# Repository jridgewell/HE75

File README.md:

# HE75

A standard 60% kebyoard (GH60 compatible) with 75 hall effects keys and an ortholinear layout.

## Prior Art

While this keyboard is my own design, I pulled from many prior keyboard designs to figure out 60% layouts and how to layout hall effect sensors.

- [MoonBoard](https://github.com/certainly1182/MoonBoard), which I used heavily for routing patterns, schematic design, and even to find code to program QMK.
- [Void Switch 65%](https://github.com/riskable/void_switch_65_pct) (and the 2 begining videos [part 1](https://www.youtube.com/watch?v=TfKz_FbZWLQ) and [part 2](https://www.youtube.com/watch?v=sFR6E_Ejot0)), for giving me a starting point.
- [HE8](https://github.com/peppapighs/HE8) (and his [writeup](https://old.reddit.com/r/MechanicalKeyboards/comments/1glk0dc/i_made_a_hall_effect_macropad_long_writeup_below/)) to confirm components work.

I also used a few community assets to start the design:
- https://github.com/ebastler/marbastlib for switches and stabalizers footprints.
- https://github.com/ai03-2725/JP60 for an up-to-date GH60 shell layout.

# Constraints while designing

1. Must fit into a 60% keyboard case
2. Must use an ortholinear layout
3. Must use hall effect keys

I bought a [Wooting 60HE module](https://wooting.io/wooting-60he-module) and case, but I just can't stand the standard keyboard layout after using a split-ortho board for years. This is my attempt to cram an ortholinear layout into the same case, keeping it as close to a normal row staggered layout as possible. I do need occasional 1-handed access to right-hand side of the keyboard, I'm not after a mock split.

The first major issue is mouting positions for GH60 keyboards (marked in red):

When putting an ortholinear layout over top of that, several of the keys conflict:

If I were using standard MX key switches, this would only require rotating those keys 90% and skipping the screws in those locations. But with a hall effect keyboard, there's a hall effect sensor on the backside of the PCB occupying the same space as the screw mount. I need to move it so that it doesn't short out or get damaged when inserting the keyboard into the case. So for three keys (Q, H, and \), the sensor is roughly 1mm out of alignment with the key switch's magnet. Hopefully this'll be ok.

# Next Steps

I haven't ordered the first set of boards yet. JLCPCB estimates $47 for the first 5 PCBs, and $142 to get them assembled. I'm hoping someone will review the design before I send it off, I'm very new to this.

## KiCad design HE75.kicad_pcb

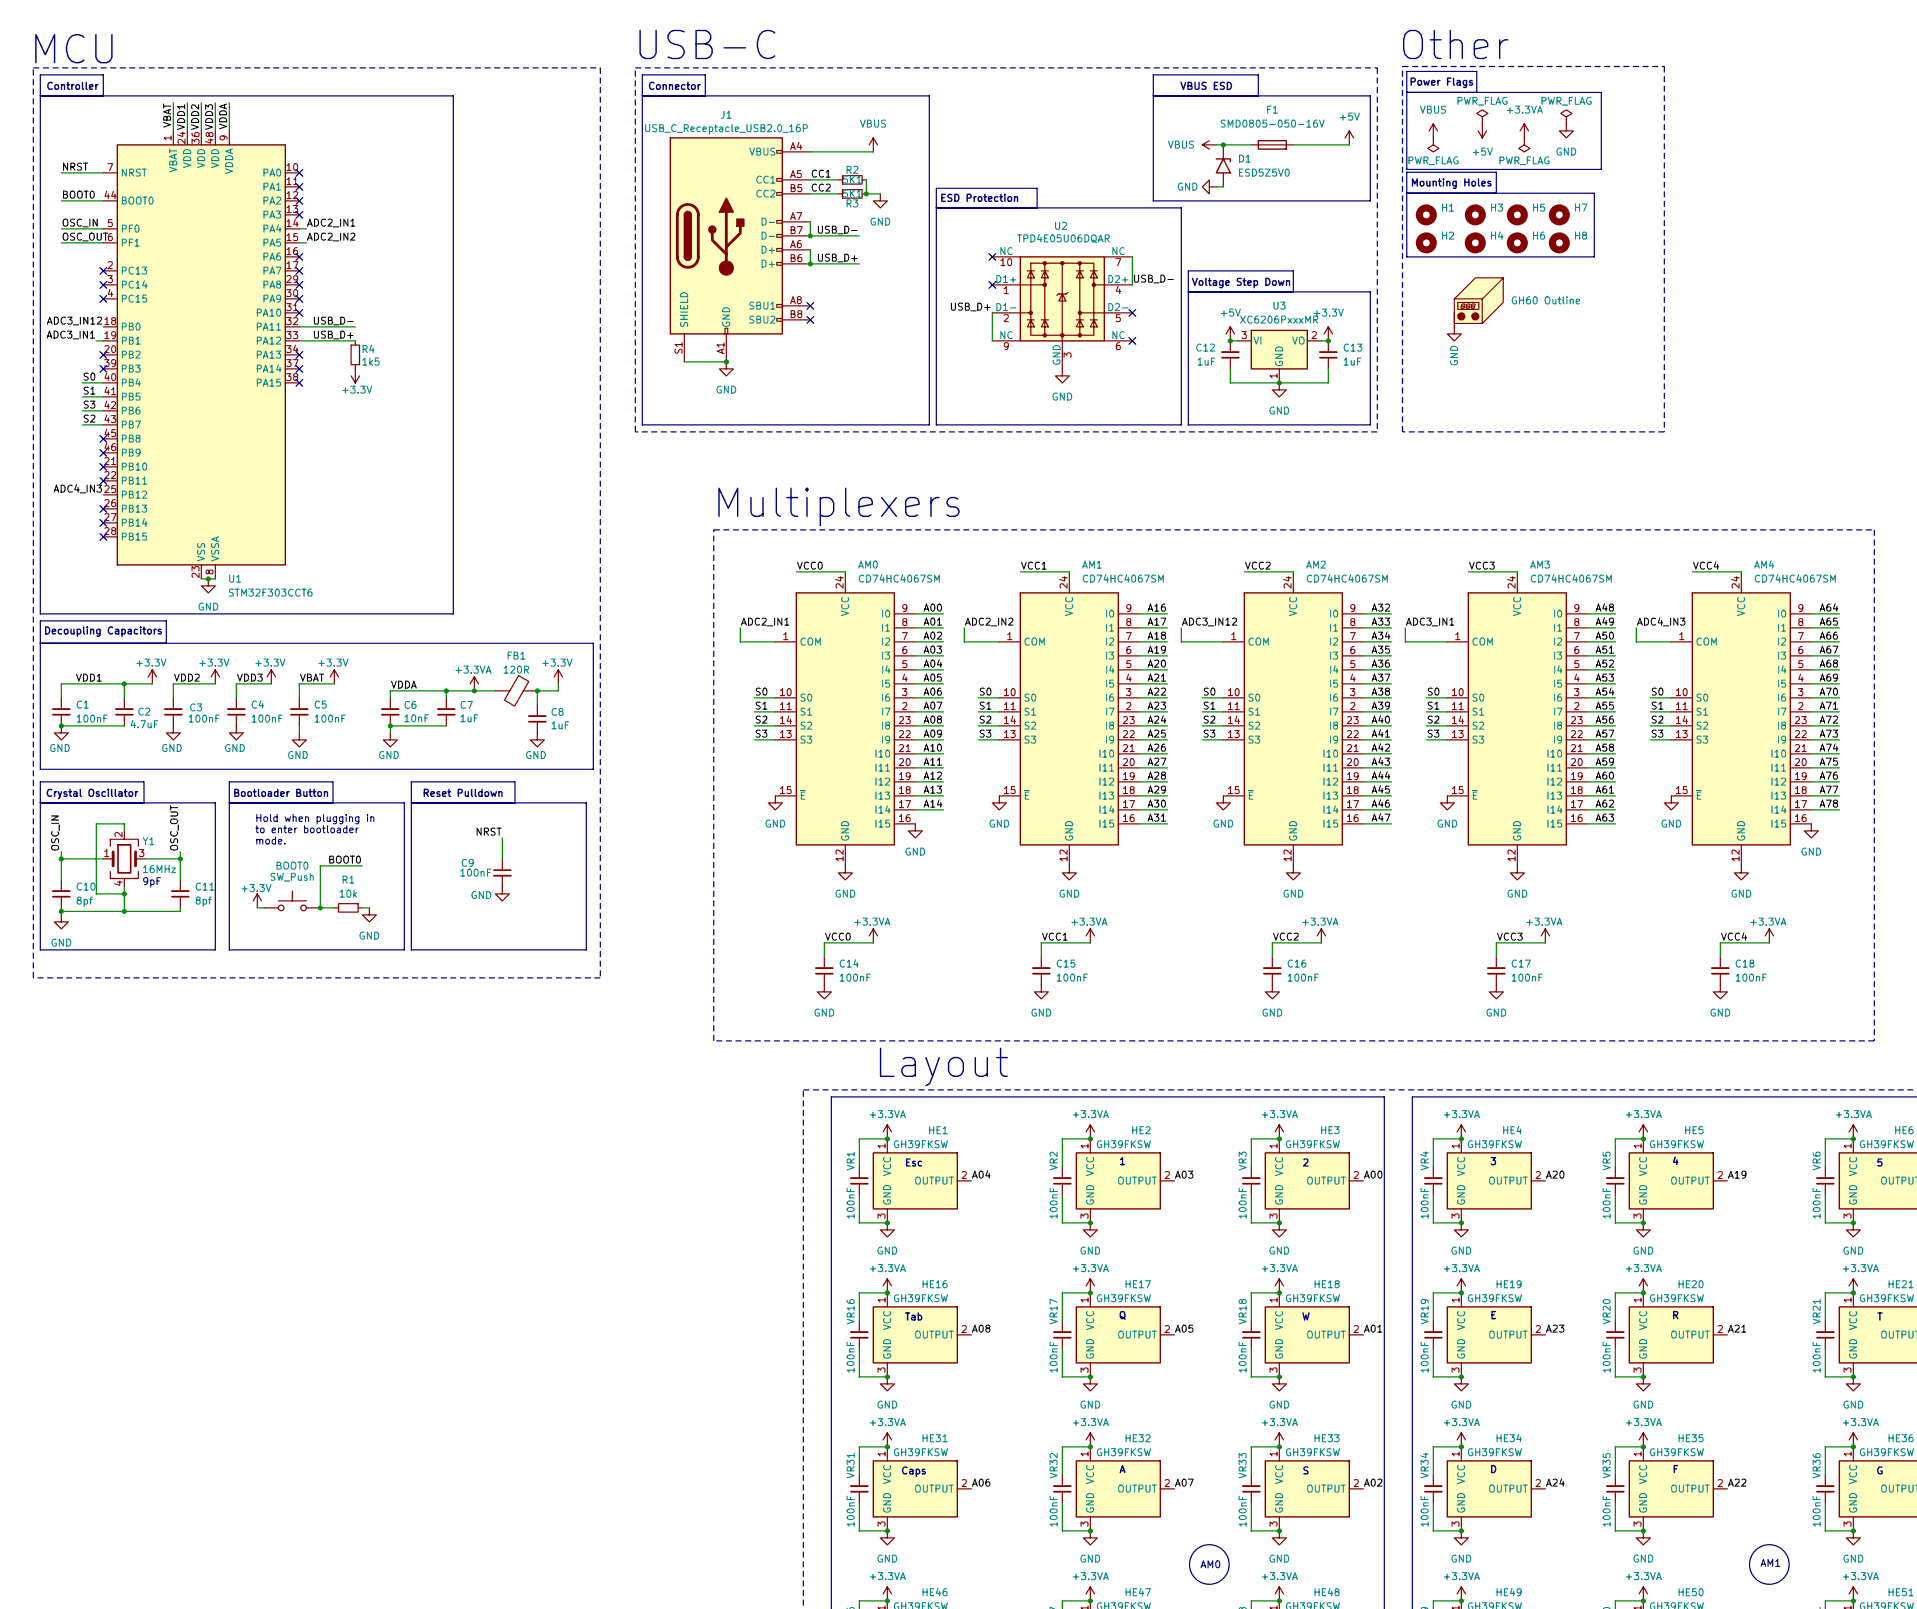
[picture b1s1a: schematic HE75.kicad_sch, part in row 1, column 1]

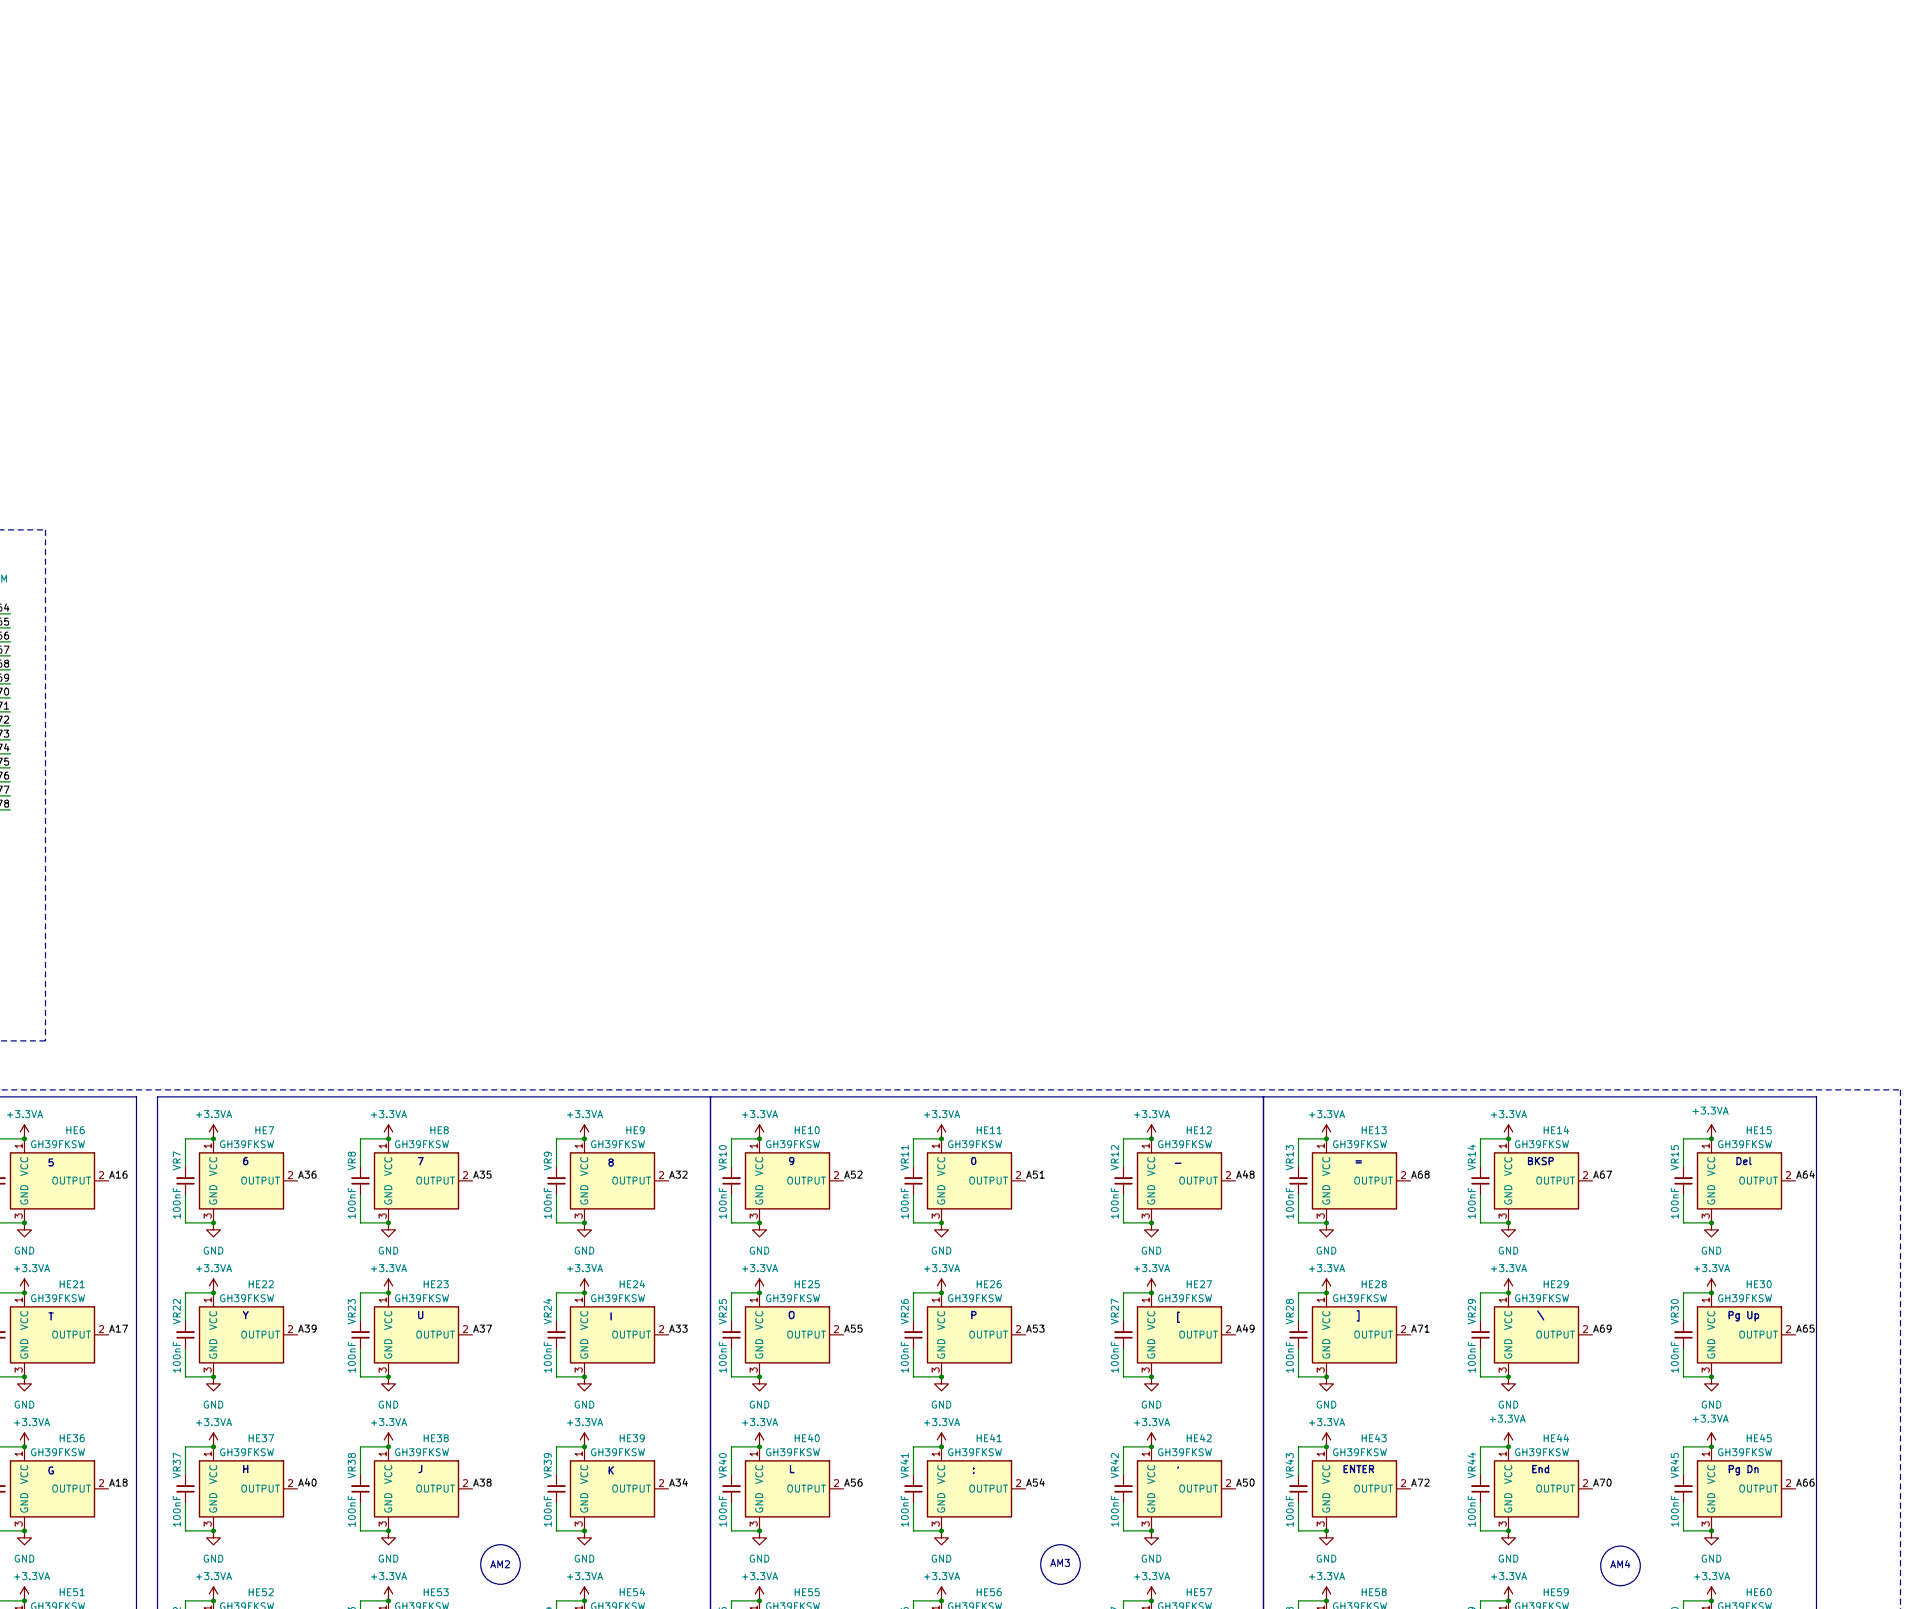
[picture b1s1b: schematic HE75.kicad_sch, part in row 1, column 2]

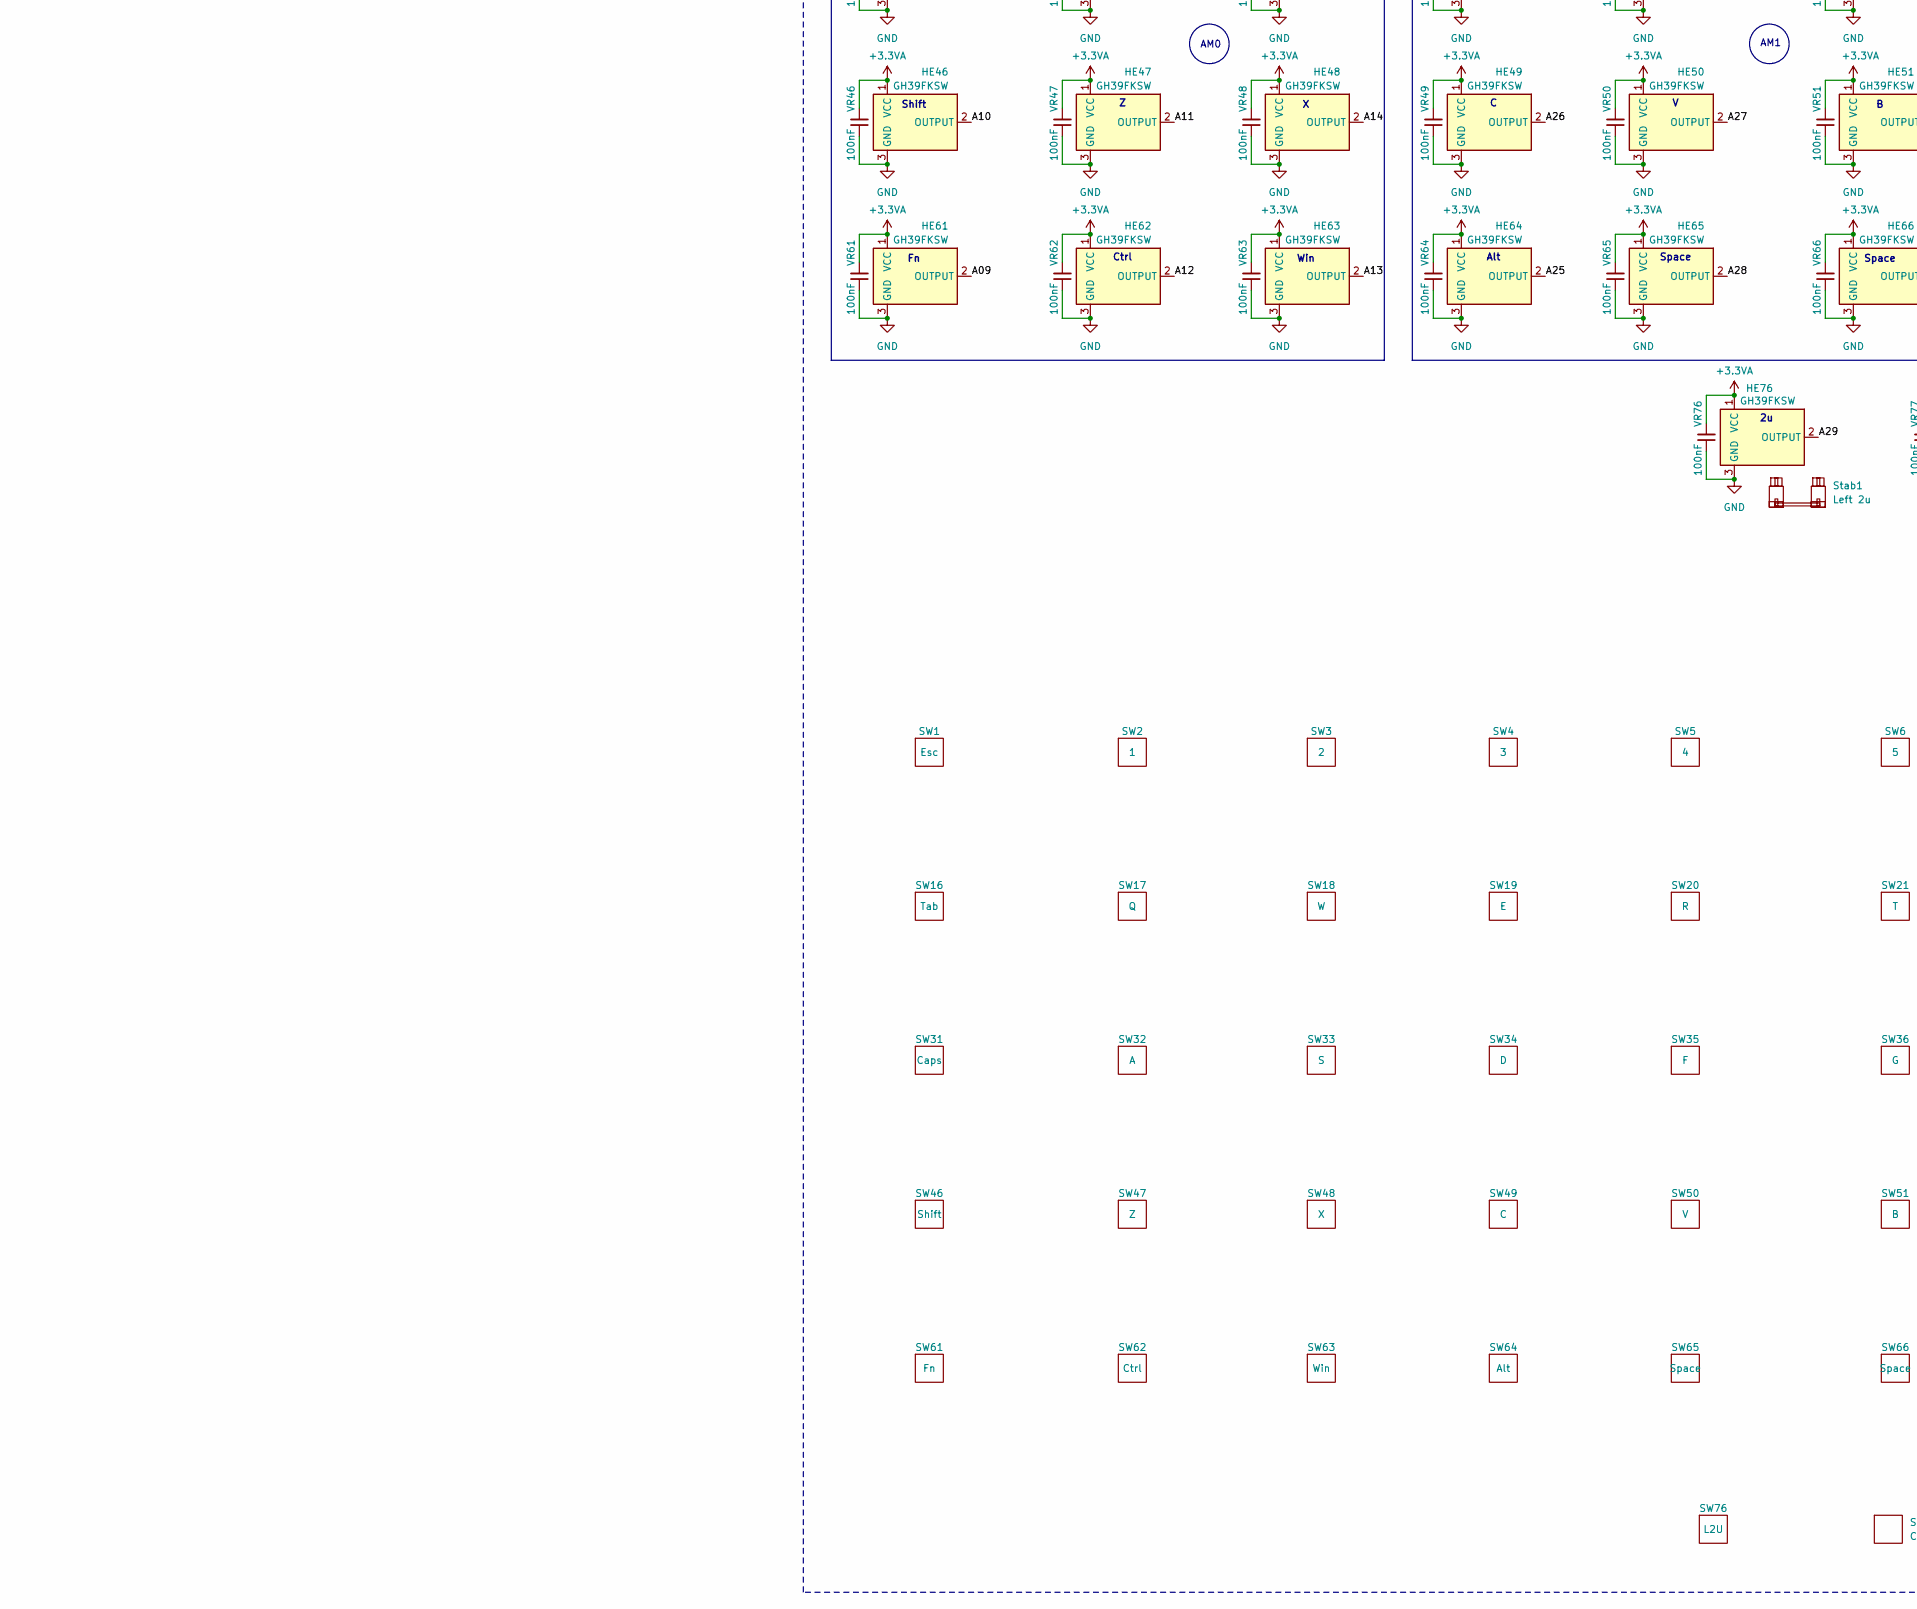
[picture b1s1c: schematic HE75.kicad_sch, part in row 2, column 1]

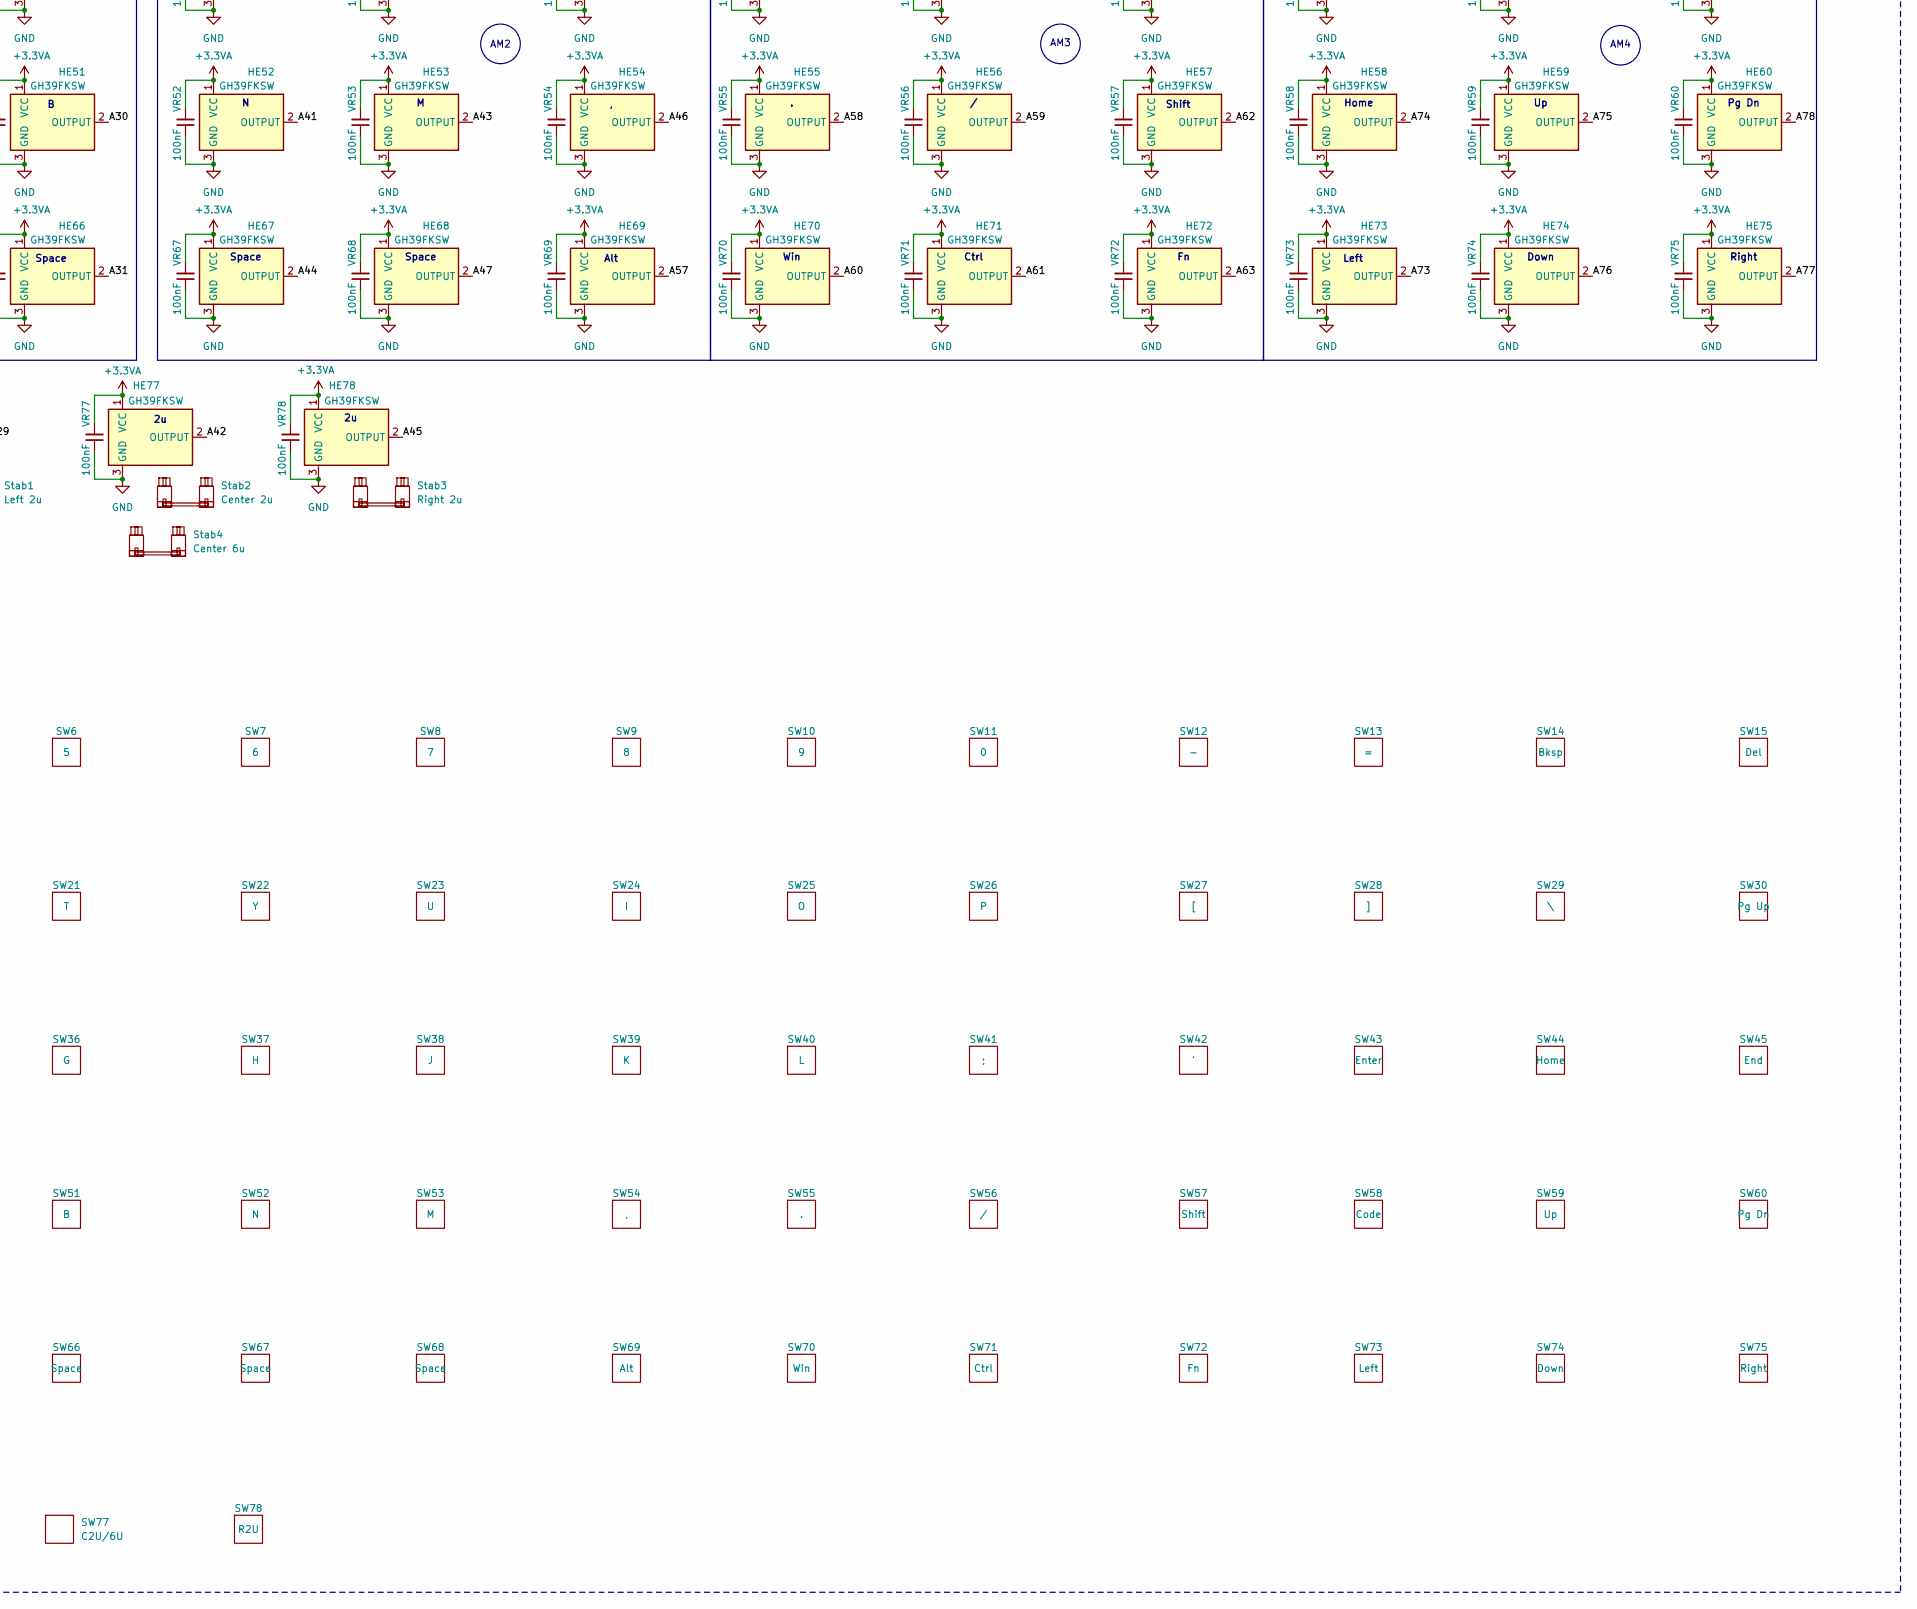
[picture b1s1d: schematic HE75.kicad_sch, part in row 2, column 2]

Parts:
AM0, AM1, AM2, AM3, AM4: CD74HC4067SM; SSOP-24_5.3x8.2mm_P0.65mm; LCSC C98457
BOOT0: SW_Push; SW_SPST_TL3342; MPN SKQGABE010; LCSC C115351
C1, C3, C4, C5, C9, C14, C15, C16, C17, C18: 100nF; Capacitor 0402; LCSC C1525
C2: 4.7uF; Capacitor 0402; LCSC C23733
C6: 10nF; Capacitor 0402; LCSC C15195
C7, C8, C12, C13: 1uF; Capacitor 0402; LCSC C52923
C10, C11: 8pf; Capacitor 0402; LCSC C472443
D1: ESD5Z5V0; D_SOD-523; Manufacturer Part Number ESD5Z5V0; LCSC C502546
F1: SMD0805-050-16V; Fuse_0805_2012Metric; Manufacturer Part Number SMD0805-050-16V; LCSC C2833485
FB1: 120R; L_0805_2012Metric; LCSC C285922
H1, H2, H3, H4, H5, H6, H7, H8: MountingHole; MountingHole_2.2mm_M2
HE1, HE2, HE3, HE4, HE5, HE6, HE7, HE8, HE9, HE10, HE11, HE12, HE13, HE14, HE15, HE16, HE17, HE18, HE19, HE20, HE21, HE22, HE23, HE24, HE25, HE26, HE27, HE28, HE29, HE30, HE31, HE32, HE33, HE34, HE35, HE36, HE37, HE38, HE39, HE40, HE41, HE42, HE43, HE44, HE45, HE46, HE47, HE48, HE49, HE50, HE51, HE52, HE53, HE54, HE55, HE56, HE57, HE58, HE59, HE60, HE61, HE62, HE63, HE64, HE65, HE66, HE67, HE68, HE69, HE70, HE71, HE72, HE73, HE74, HE75, HE76, HE77, HE78: GH39FKSW; Hall Effect Sensor SOT-23; LCSC C266230
J1: USB_C_Receptacle_USB2.0_16P; USB_C_Receptacle_HRO_TYPE-C-31-M-12; MPN TYPE-C-31-M-12; LCSC C165948
O1: GH60 Outline; 60_Outline
R1: 10k; R_0402_1005Metric; LCSC C25744
R2, R3: 5K1; R_0402_1005Metric; LCSC C25905
R4: 1k5; R_0402_1005Metric; LCSC C25867
SW1: Esc; 1u MX Hall Effect
SW2: 1; 1u MX Hall Effect
SW3: 2; 1u MX Hall Effect
SW4: 3; 1u MX Hall Effect
SW5: 4; 1u MX Hall Effect
SW6: 5; 1u MX Hall Effect
SW7: 6; 1u MX Hall Effect
SW8: 7; 1u MX Hall Effect
SW9: 8; 1u MX Hall Effect
SW10: 9; 1u MX Hall Effect
SW11: 0; 1u MX Hall Effect
SW12: -; 1u MX Hall Effect
SW13: =; 1u MX Hall Effect
SW14: Bksp; 1u MX Hall Effect
SW15: Del; 1u MX Hall Effect
SW16: Tab; 1u MX Hall Effect
SW17: Q; 1u MX Hall Effect
SW18: W; 1u MX Hall Effect
SW19: E; 1u MX Hall Effect
SW20: R; 1u MX Hall Effect
SW21: T; 1u MX Hall Effect
SW22: Y; 1u MX Hall Effect
SW23: U; 1u MX Hall Effect
SW24: I; 1u MX Hall Effect
SW25: O; 1u MX Hall Effect
SW26: P; 1u MX Hall Effect
SW27: [; 1u MX Hall Effect
SW28: ]; 1u MX Hall Effect
SW29: \; 1u MX Hall Effect
SW30: Pg Up; 1u MX Hall Effect
SW31: Caps; 1u MX Hall Effect
SW32: A; 1u MX Hall Effect
SW33: S; 1u MX Hall Effect
SW34: D; 1u MX Hall Effect
SW35: F; 1u MX Hall Effect
SW36: G; 1u MX Hall Effect
SW37: H; 1u MX Hall Effect
SW38: J; 1u MX Hall Effect
SW39: K; 1u MX Hall Effect
SW40: L; 1u MX Hall Effect
SW41: ;; 1u MX Hall Effect
SW42: '; 1u MX Hall Effect
SW43: Enter; 1u MX Hall Effect
SW44: Home; 1u MX Hall Effect
SW45: End; 1u MX Hall Effect
SW46, SW57: Shift; 1u MX Hall Effect
SW47: Z; 1u MX Hall Effect
SW48: X; 1u MX Hall Effect
SW49: C; 1u MX Hall Effect
SW50: V; 1u MX Hall Effect
SW51: B; 1u MX Hall Effect
SW52: N; 1u MX Hall Effect
SW53: M; 1u MX Hall Effect
SW54: ,; 1u MX Hall Effect
SW55: .; 1u MX Hall Effect
SW56: /; 1u MX Hall Effect
SW58: Code; 1u MX Hall Effect
SW59: Up; 1u MX Hall Effect
SW60: Pg Dn; 1u MX Hall Effect
SW61, SW72: Fn; 1u MX Hall Effect
SW62, SW71: Ctrl; 1u MX Hall Effect
SW63, SW70: Win; 1u MX Hall Effect
SW64, SW69: Alt; 1u MX Hall Effect
SW65, SW66, SW67, SW68: Space; 1u MX Hall Effect
SW73: Left; 1u MX Hall Effect
SW74: Down; 1u MX Hall Effect
SW75: Right; 1u MX Hall Effect
SW76: L2U; 1u MX Hall Effect
SW77: C2U/6U; 1u MX Hall Effect
SW78: R2U; 1u MX Hall Effect
Stab1: Left 2u; STAB_MX_2u
Stab2: Center 2u; STAB_MX_2u
Stab3: Right 2u; STAB_MX_2u
Stab4: Center 6u; STAB_MX_6u
U1: STM32F303CCT6; LQFP-48_7x7mm_P0.5mm; LCSC C81523
U2: TPD4E05U06DQAR; USON-10_2.5x1.0mm_P0.5mm; LCSC C138714
U3: XC6206PxxxMR; SOT-23-3; MPN XC6206P332MR-G; LCSC C5446
VR1, VR2, VR3, VR4, VR5, VR6, VR7, VR8, VR9, VR10, VR11, VR12, VR13, VR14, VR15, VR16, VR17, VR18, VR19, VR20, VR21, VR22, VR23, VR24, VR25, VR26, VR27, VR28, VR29, VR30, VR31, VR32, VR33, VR34, VR35, VR36, VR37, VR38, VR39, VR40, VR41, VR42, VR43, VR44, VR45, VR46, VR47, VR48, VR49, VR50, VR51, VR52, VR53, VR54, VR55, VR56, VR57, VR58, VR59, VR60, VR61, VR62, VR63, VR64, VR65, VR66, VR67, VR68, VR69, VR70, VR71, VR72, VR73, VR74, VR75, VR76, VR77, VR78: 100nF; Capacitor 0402; LCSC C1525
Y1: 16MHz; Crystal_SMD_3225-4Pin_3.2x2.5mm; LCSC C13738

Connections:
+3.3V: BOOT0.1, C1.2, C2.2, C3.2, C4.2, C5.2, C8.2, C13.2, FB1.1, R4.2, U1.1 (VBAT), U1.24 (VDD), U1.36 (VDD), U1.48 (VDD), U3.2 (VO)
+3.3VA: AM0.24 (VCC), AM1.24 (VCC), AM2.24 (VCC), AM3.24 (VCC), AM4.24 (VCC), C6.2, C7.2, C14.2, C15.2, C16.2, C17.2, C18.2, FB1.2, HE1.1 (VCC), HE2.1 (VCC), HE3.1 (VCC), HE4.1 (VCC), HE5.1 (VCC), HE6.1 (VCC), HE7.1 (VCC), HE8.1 (VCC), HE9.1 (VCC), HE10.1 (VCC), HE11.1 (VCC), HE12.1 (VCC), HE13.1 (VCC), HE14.1 (VCC), HE15.1 (VCC), HE16.1 (VCC), HE17.1 (VCC), HE18.1 (VCC), HE19.1 (VCC), HE20.1 (VCC), HE21.1 (VCC), HE22.1 (VCC), HE23.1 (VCC), HE24.1 (VCC), HE25.1 (VCC), HE26.1 (VCC), HE27.1 (VCC), HE28.1 (VCC), HE29.1 (VCC), HE30.1 (VCC), HE31.1 (VCC), HE32.1 (VCC), HE33.1 (VCC), HE34.1 (VCC), HE35.1 (VCC), HE36.1 (VCC), HE37.1 (VCC), HE38.1 (VCC), HE39.1 (VCC), HE40.1 (VCC), HE41.1 (VCC), HE42.1 (VCC), HE43.1 (VCC), HE44.1 (VCC), HE45.1 (VCC), HE46.1 (VCC), HE47.1 (VCC), HE48.1 (VCC), HE49.1 (VCC), HE50.1 (VCC), HE51.1 (VCC), HE52.1 (VCC), HE53.1 (VCC), HE54.1 (VCC), HE55.1 (VCC), HE56.1 (VCC), HE57.1 (VCC), HE58.1 (VCC), HE59.1 (VCC), HE60.1 (VCC), HE61.1 (VCC), HE62.1 (VCC), HE63.1 (VCC), HE64.1 (VCC), HE65.1 (VCC), HE66.1 (VCC), HE67.1 (VCC), HE68.1 (VCC), HE69.1 (VCC), HE70.1 (VCC), HE71.1 (VCC), HE72.1 (VCC), HE73.1 (VCC), HE74.1 (VCC), HE75.1 (VCC), HE76.1 (VCC), HE77.1 (VCC), HE78.1 (VCC), U1.9 (VDDA), VR1.2, VR2.2, VR3.2, VR4.2, VR5.2, VR6.2, VR7.2, VR8.2, VR9.2, VR10.2, VR11.2, VR12.2, VR13.2, VR14.2, VR15.2, VR16.2, VR17.2, VR18.2, VR19.2, VR20.2, VR21.2, VR22.2, VR23.2, VR24.2, VR25.2, VR26.2, VR27.2, VR28.2, VR29.2, VR30.2, VR31.2, VR32.2, VR33.2, VR34.2, VR35.2, VR36.2, VR37.2, VR38.2, VR39.2, VR40.2, VR41.2, VR42.2, VR43.2, VR44.2, VR45.2, VR46.2, VR47.2, VR48.2, VR49.2, VR50.2, VR51.2, VR52.2, VR53.2, VR54.2, VR55.2, VR56.2, VR57.2, VR58.2, VR59.2, VR60.2, VR61.2, VR62.2, VR63.2, VR64.2, VR65.2, VR66.2, VR67.2, VR68.2, VR69.2, VR70.2, VR71.2, VR72.2, VR73.2, VR74.2, VR75.2, VR76.2, VR77.2, VR78.2
+5V: C12.2, F1.2, U3.3 (VI)
/A00: AM0.9 (I0), HE3.2 (OUTPUT)
/A01: AM0.8 (I1), HE18.2 (OUTPUT)
/A02: AM0.7 (I2), HE33.2 (OUTPUT)
/A03: AM0.6 (I3), HE2.2 (OUTPUT)
/A04: AM0.5 (I4), HE1.2 (OUTPUT)
/A05: AM0.4 (I5), HE17.2 (OUTPUT)
/A06: AM0.3 (I6), HE31.2 (OUTPUT)
/A07: AM0.2 (I7), HE32.2 (OUTPUT)
/A08: AM0.23 (I8), HE16.2 (OUTPUT)
/A09: AM0.22 (I9), HE61.2 (OUTPUT)
/A10: AM0.21 (I10), HE46.2 (OUTPUT)
/A11: AM0.20 (I11), HE47.2 (OUTPUT)
/A12: AM0.19 (I12), HE62.2 (OUTPUT)
/A13: AM0.18 (I13), HE63.2 (OUTPUT)
/A14: AM0.17 (I14), HE48.2 (OUTPUT)
/A16: AM1.9 (I0), HE6.2 (OUTPUT)
/A17: AM1.8 (I1), HE21.2 (OUTPUT)
/A18: AM1.7 (I2), HE36.2 (OUTPUT)
/A19: AM1.6 (I3), HE5.2 (OUTPUT)
/A20: AM1.5 (I4), HE4.2 (OUTPUT)
/A21: AM1.4 (I5), HE20.2 (OUTPUT)
/A22: AM1.3 (I6), HE35.2 (OUTPUT)
/A23: AM1.2 (I7), HE19.2 (OUTPUT)
/A24: AM1.23 (I8), HE34.2 (OUTPUT)
/A25: AM1.22 (I9), HE64.2 (OUTPUT)
/A26: AM1.21 (I10), HE49.2 (OUTPUT)
/A27: AM1.20 (I11), HE50.2 (OUTPUT)
/A28: AM1.19 (I12), HE65.2 (OUTPUT)
/A29: AM1.18 (I13), HE76.2 (OUTPUT)
/A30: AM1.17 (I14), HE51.2 (OUTPUT)
/A31: AM1.16 (I15), HE66.2 (OUTPUT)
/A32: AM2.9 (I0), HE9.2 (OUTPUT)
/A33: AM2.8 (I1), HE24.2 (OUTPUT)
/A34: AM2.7 (I2), HE39.2 (OUTPUT)
/A35: AM2.6 (I3), HE8.2 (OUTPUT)
/A36: AM2.5 (I4), HE7.2 (OUTPUT)
/A37: AM2.4 (I5), HE23.2 (OUTPUT)
/A38: AM2.3 (I6), HE38.2 (OUTPUT)
/A39: AM2.2 (I7), HE22.2 (OUTPUT)
/A40: AM2.23 (I8), HE37.2 (OUTPUT)
/A41: AM2.22 (I9), HE52.2 (OUTPUT)
/A42: AM2.21 (I10), HE77.2 (OUTPUT)
/A43: AM2.20 (I11), HE53.2 (OUTPUT)
/A44: AM2.19 (I12), HE67.2 (OUTPUT)
/A45: AM2.18 (I13), HE78.2 (OUTPUT)
/A46: AM2.17 (I14), HE54.2 (OUTPUT)
/A47: AM2.16 (I15), HE68.2 (OUTPUT)
/A48: AM3.9 (I0), HE12.2 (OUTPUT)
/A49: AM3.8 (I1), HE27.2 (OUTPUT)
/A50: AM3.7 (I2), HE42.2 (OUTPUT)
/A51: AM3.6 (I3), HE11.2 (OUTPUT)
/A52: AM3.5 (I4), HE10.2 (OUTPUT)
/A53: AM3.4 (I5), HE26.2 (OUTPUT)
/A54: AM3.3 (I6), HE41.2 (OUTPUT)
/A55: AM3.2 (I7), HE25.2 (OUTPUT)
/A56: AM3.23 (I8), HE40.2 (OUTPUT)
/A57: AM3.22 (I9), HE69.2 (OUTPUT)
/A58: AM3.21 (I10), HE55.2 (OUTPUT)
/A59: AM3.20 (I11), HE56.2 (OUTPUT)
/A60: AM3.19 (I12), HE70.2 (OUTPUT)
/A61: AM3.18 (I13), HE71.2 (OUTPUT)
/A62: AM3.17 (I14), HE57.2 (OUTPUT)
/A63: AM3.16 (I15), HE72.2 (OUTPUT)
/A64: AM4.9 (I0), HE15.2 (OUTPUT)
/A65: AM4.8 (I1), HE30.2 (OUTPUT)
/A66: AM4.7 (I2), HE45.2 (OUTPUT)
/A67: AM4.6 (I3), HE14.2 (OUTPUT)
/A68: AM4.5 (I4), HE13.2 (OUTPUT)
/A69: AM4.4 (I5), HE29.2 (OUTPUT)
/A70: AM4.3 (I6), HE44.2 (OUTPUT)
/A71: AM4.2 (I7), HE28.2 (OUTPUT)
/A72: AM4.23 (I8), HE43.2 (OUTPUT)
/A73: AM4.22 (I9), HE73.2 (OUTPUT)
/A74: AM4.21 (I10), HE58.2 (OUTPUT)
/A75: AM4.20 (I11), HE59.2 (OUTPUT)
/A76: AM4.19 (I12), HE74.2 (OUTPUT)
/A77: AM4.18 (I13), HE75.2 (OUTPUT)
/A78: AM4.17 (I14), HE60.2 (OUTPUT)
/ADC2_IN1: AM0.1 (COM), U1.14 (PA4)
/ADC2_IN2: AM1.1 (COM), U1.15 (PA5)
/ADC3_IN1: AM3.1 (COM), U1.19 (PB1)
/ADC3_IN12: AM2.1 (COM), U1.18 (PB0)
/ADC4_IN3: AM4.1 (COM), U1.25 (PB12)
/BOOT0: BOOT0.2, R1.2, U1.44 (BOOT0)
/CC1: J1.A5 (CC1), R2.1
/CC2: J1.B5 (CC2), R3.1
/NRST: C9.1, U1.7 (NRST)
/OSC_IN: C10.2, U1.5 (PF0), Y1.1
/OSC_OUT: C11.2, U1.6 (PF1), Y1.3
/S0: AM0.10 (S0), AM1.10 (S0), AM2.10 (S0), AM3.10 (S0), AM4.10 (S0), U1.40 (PB4)
/S1: AM0.11 (S1), AM1.11 (S1), AM2.11 (S1), AM3.11 (S1), AM4.11 (S1), U1.41 (PB5)
/S2: AM0.14 (S2), AM1.14 (S2), AM2.14 (S2), AM3.14 (S2), AM4.14 (S2), U1.43 (PB7)
/S3: AM0.13 (S3), AM1.13 (S3), AM2.13 (S3), AM3.13 (S3), AM4.13 (S3), U1.42 (PB6)
/USB_D+: J1.A6 (D+), J1.B6 (D+), R4.1, U1.33 (PA12), U2.2 (D1-), U2.9 (NC)
/USB_D-: J1.A7 (D-), J1.B7 (D-), U1.32 (PA11), U2.4 (D2+), U2.7 (NC)
GND: AM0.12 (GND), AM0.15 (~E), AM0.16 (I15), AM1.12 (GND), AM1.15 (~E), AM2.12 (GND), AM2.15 (~E), AM3.12 (GND), AM3.15 (~E), AM4.12 (GND), AM4.15 (~E), AM4.16 (I15), C1.1, C2.1, C3.1, C4.1, C5.1, C6.1, C7.1, C8.1, C9.2, C10.1, C11.1, C12.1, C13.1, C14.1, C15.1, C16.1, C17.1, C18.1, D1.2 (A2), HE1.3 (GND), HE2.3 (GND), HE3.3 (GND), HE4.3 (GND), HE5.3 (GND), HE6.3 (GND), HE7.3 (GND), HE8.3 (GND), HE9.3 (GND), HE10.3 (GND), HE11.3 (GND), HE12.3 (GND), HE13.3 (GND), HE14.3 (GND), HE15.3 (GND), HE16.3 (GND), HE17.3 (GND), HE18.3 (GND), HE19.3 (GND), HE20.3 (GND), HE21.3 (GND), HE22.3 (GND), HE23.3 (GND), HE24.3 (GND), HE25.3 (GND), HE26.3 (GND), HE27.3 (GND), HE28.3 (GND), HE29.3 (GND), HE30.3 (GND), HE31.3 (GND), HE32.3 (GND), HE33.3 (GND), HE34.3 (GND), HE35.3 (GND), HE36.3 (GND), HE37.3 (GND), HE38.3 (GND), HE39.3 (GND), HE40.3 (GND), HE41.3 (GND), HE42.3 (GND), HE43.3 (GND), HE44.3 (GND), HE45.3 (GND), HE46.3 (GND), HE47.3 (GND), HE48.3 (GND), HE49.3 (GND), HE50.3 (GND), HE51.3 (GND), HE52.3 (GND), HE53.3 (GND), HE54.3 (GND), HE55.3 (GND), HE56.3 (GND), HE57.3 (GND), HE58.3 (GND), HE59.3 (GND), HE60.3 (GND), HE61.3 (GND), HE62.3 (GND), HE63.3 (GND), HE64.3 (GND), HE65.3 (GND), HE66.3 (GND), HE67.3 (GND), HE68.3 (GND), HE69.3 (GND), HE70.3 (GND), HE71.3 (GND), HE72.3 (GND), HE73.3 (GND), HE74.3 (GND), HE75.3 (GND), HE76.3 (GND), HE77.3 (GND), HE78.3 (GND), J1.A1 (GND), J1.A12 (GND), J1.B1 (GND), J1.B12 (GND), J1.S1 (SHIELD), O1.1 (PAD), R1.1, R2.2, R3.2, U1.8 (VSSA), U1.23 (VSS), U1.35 (VSS), U1.47 (VSS), U2.3 (GND), U2.8 (GND), U3.1 (GND), VR1.1, VR2.1, VR3.1, VR4.1, VR5.1, VR6.1, VR7.1, VR8.1, VR9.1, VR10.1, VR11.1, VR12.1, VR13.1, VR14.1, VR15.1, VR16.1, VR17.1, VR18.1, VR19.1, VR20.1, VR21.1, VR22.1, VR23.1, VR24.1, VR25.1, VR26.1, VR27.1, VR28.1, VR29.1, VR30.1, VR31.1, VR32.1, VR33.1, VR34.1, VR35.1, VR36.1, VR37.1, VR38.1, VR39.1, VR40.1, VR41.1, VR42.1, VR43.1, VR44.1, VR45.1, VR46.1, VR47.1, VR48.1, VR49.1, VR50.1, VR51.1, VR52.1, VR53.1, VR54.1, VR55.1, VR56.1, VR57.1, VR58.1, VR59.1, VR60.1, VR61.1, VR62.1, VR63.1, VR64.1, VR65.1, VR66.1, VR67.1, VR68.1, VR69.1, VR70.1, VR71.1, VR72.1, VR73.1, VR74.1, VR75.1, VR76.1, VR77.1, VR78.1, Y1.2, Y1.4
VBUS: D1.1 (A1), F1.1, J1.A4 (VBUS), J1.A9 (VBUS), J1.B4 (VBUS), J1.B9 (VBUS)

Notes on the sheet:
Hold when plugging in to enter bootloader mode.
Pg Up
Pg Dn
Alt
BKSP
Home
MCU
Del
Space
Caps
USB-C
Mounting Holes
Layout
9pF
Down
Multiplexers
Decoupling Capacitors
AM0
Controller
Reset Pulldown
Shift
Crystal Oscillator
ESD Protection
Ctrl
Esc
Power Flags
Voltage Step Down
Win
AM3
VBUS ESD
Left
Right
AM2
Other
ENTER
AM4
Bootloader Button
AM1
Tab
End

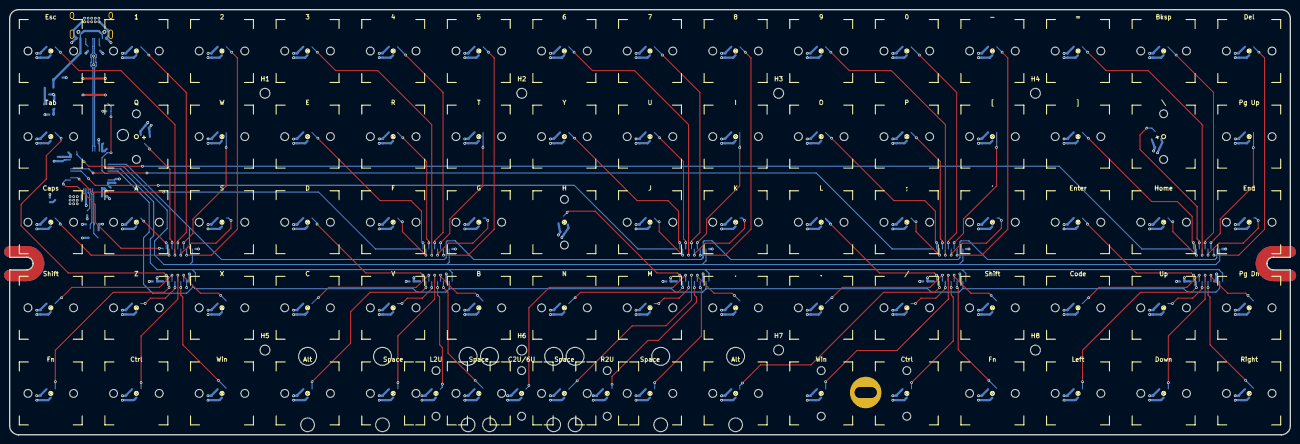
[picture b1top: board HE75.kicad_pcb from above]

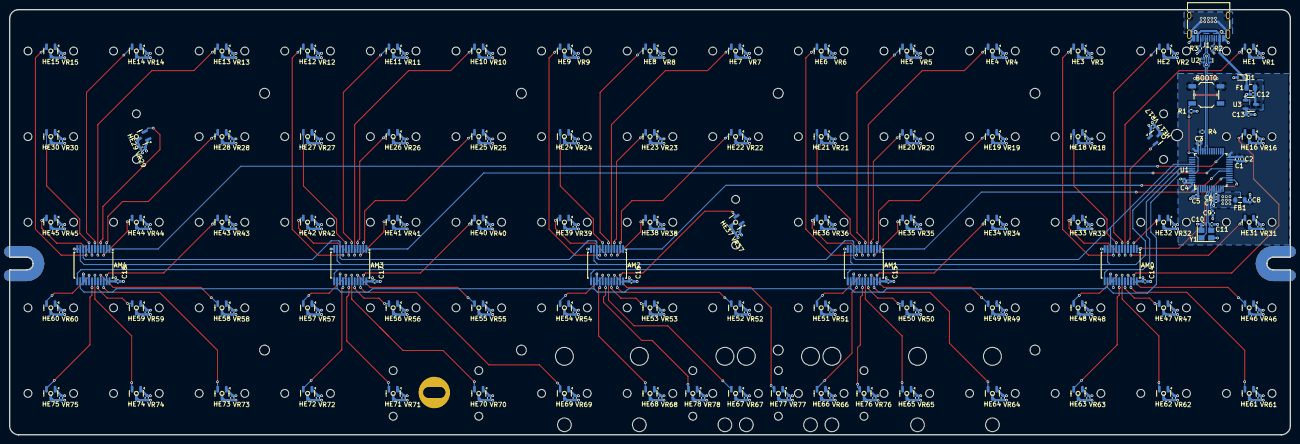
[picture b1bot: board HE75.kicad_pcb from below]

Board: 4 copper layers, 285.0 x 94.6 mm, 283 parts (192 on the bottom side), 100 nets.

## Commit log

2025-01-01 Init
2025-01-01 Cleanup
2025-01-02 Fix sot-143b footprint
2025-01-03 Fills
2025-01-04 Before attempting MCU rotation
2025-01-04 Complete
2025-01-05 Add 6u spacebar stabalizers
2025-01-05 Adjusting tracks and silkscreens
2025-01-05 Fixes for JLCPCB
2025-01-05 Rotate silkscreens
2025-01-05 Add readme
2025-01-05 Fix markdown images
2025-01-05 Update JLCPCB files
2025-01-05 Slightly adjust track routing
2025-01-08 Remove unused footprint
2025-01-08 Adjust centering silkscreens
2025-01-08 Add decoupling capacitors to analog multiplexers
2025-01-08 Rename schematic section
2025-01-08 Update JLCPCB gerbers
